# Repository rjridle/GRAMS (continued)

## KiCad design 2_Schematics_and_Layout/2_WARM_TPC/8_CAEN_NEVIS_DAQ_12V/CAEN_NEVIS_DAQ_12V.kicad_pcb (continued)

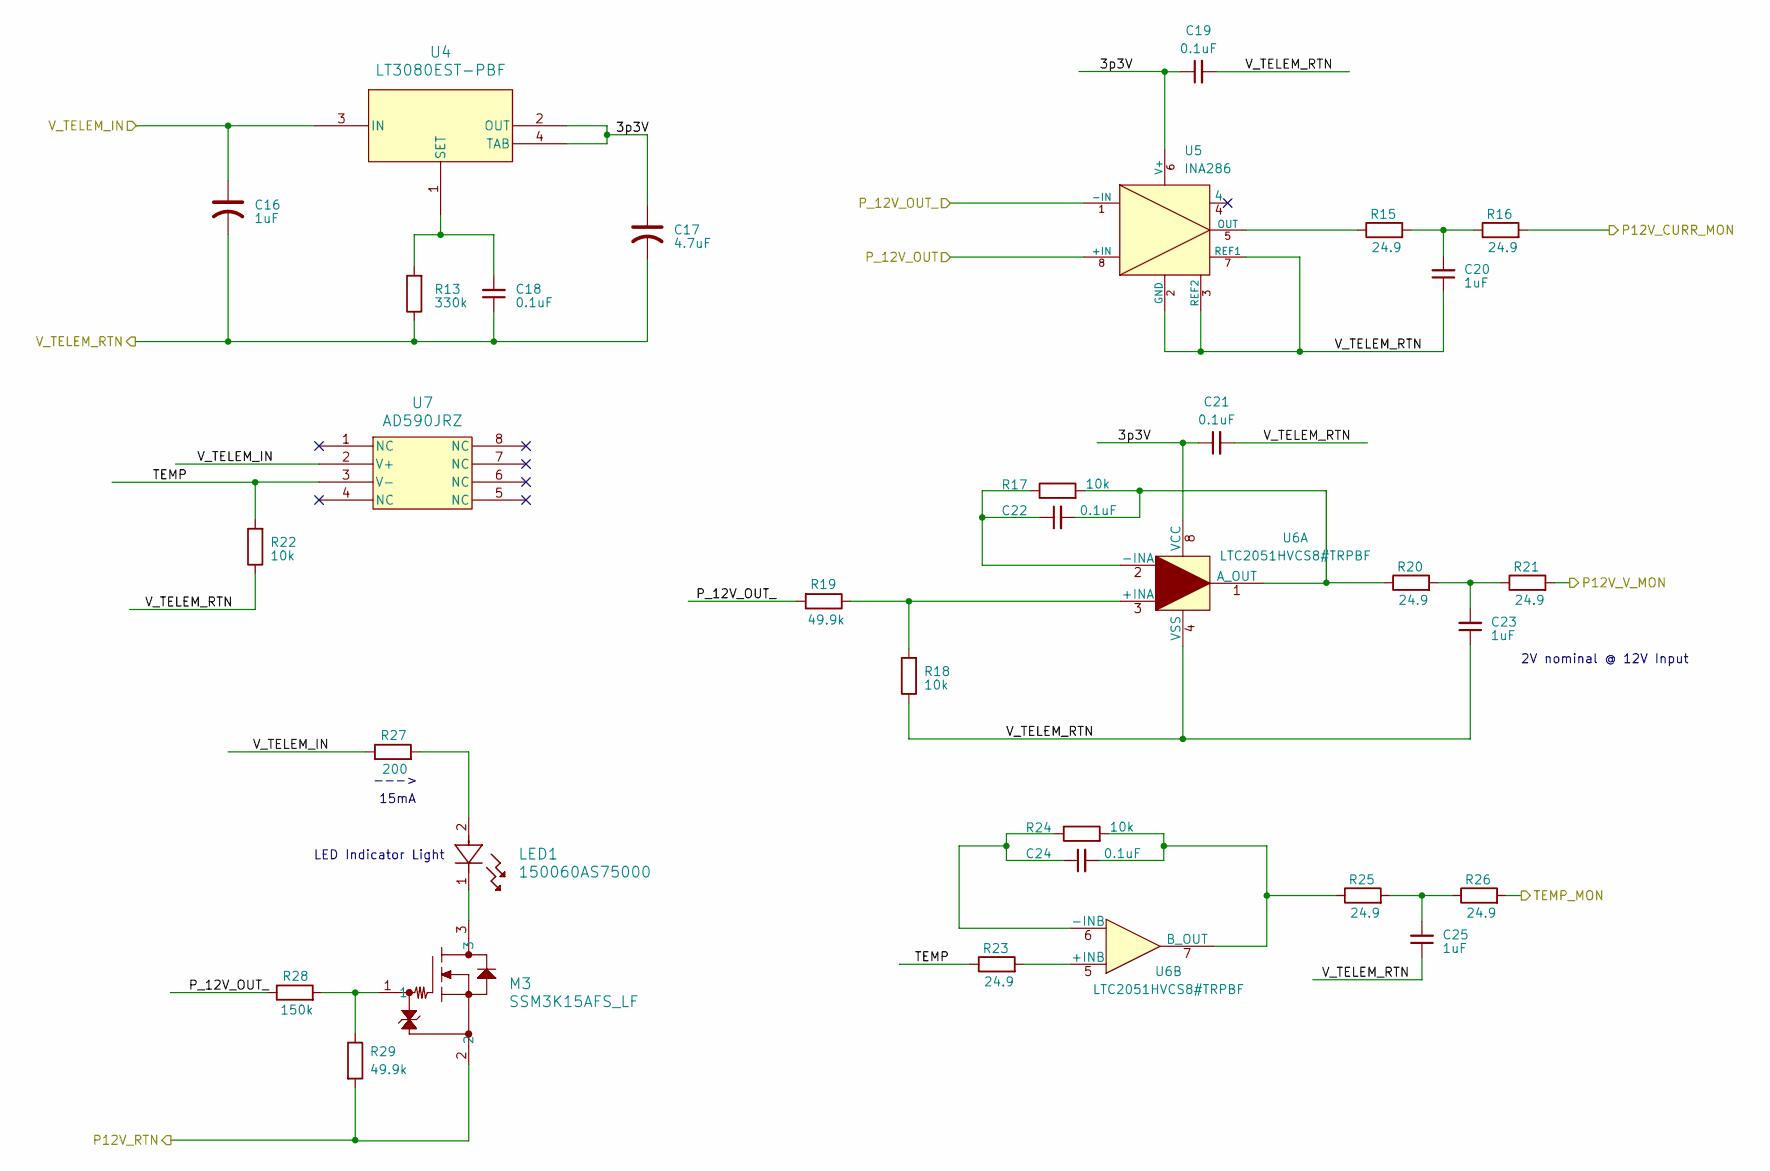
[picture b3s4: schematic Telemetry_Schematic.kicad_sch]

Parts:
C16: 1uF; CP_EIA-3216-10_Kemet-I; Man. Part Num TAJA105K016RNJ
C17: 4.7uF; CP_EIA-3216-10_Kemet-I; Man. Part Num TAJA475K016RNJ
C18: 0.1uF; C_0603_1608Metric; Man. Part Num CC0603KRX7R7BB104
C19, C21, C22, C24: 0.1uF; C_0402_1005Metric; Man. Part Num CL05B104KP5NNNC
C20, C23, C25: 1uF; C_0603_1608Metric; Man. Part Num CL10B105KO8NNNC
LED1: 150060AS75000; LED_0AS75000_WRE; Man. Part Num 150060AS75000
M3: SSM3K15AFS_LF; SSM_TOS; Man. Part Num SSM3K15AFS,LF
R13: 330k; R_0603_1608Metric; Man. Part Num ERA-3AEB334V
R15, R16, R20, R21, R23, R25, R26: 24.9; R_0603_1608Metric; Man. Part Num RNCF0603TKY24R9
R17, R24: 10k; R_0402_1005Metric; Man. Part Num RNCF0402BTE10K0
R18, R22: 10k; R_0603_1608Metric; Man. Part Num ERA-3AEB103V
R19: 49.9k; R_0603_1608Metric; Man. Part Num ERA-3AED4992V
R27: 200; R_0603_1608Metric; Man. Part Num RC0603JR-07200RL
R28: 150k; R_0603_1608Metric; Man. Part Num RK73B1JTTD154J
R29: 49.9k; R_0603_1608Metric; Man. Part Num RN73H1JTTD4992B10
U4: LT3080EST-PBF; SOT-3_ST_LIT; Man. Part Num LT3080EST#PBF
U5: INA286; INA28x_8SOIC; Man. Part Num INA286AIDR
U6: LTC2051HVCS8#TRPBF; R_8_ADI; Man. Part Num LTC2051HVCS8#TRPBF
U7: AD590JRZ; R_8_ADI; Man. Part Num AD590JRZ

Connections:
/P12V_I_MON: R16.2; also elsewhere on the board
/P12V_OUT: U5.8 (+IN); also elsewhere on the board
/P12V_OUT_: R19.2, R28.1, U5.1 (-IN); also elsewhere on the board
/P12V_V_MON: R21.2; also elsewhere on the board
/TEMP_MON: R26.2; also elsewhere on the board
/Telemetry_Schematic/3p3V: C17.1, C19.1, C21.1, U4.2 (OUT), U4.4 (TAB), U5.6 (V+), U6.8 (VCC)
/Telemetry_Schematic/TEMP: R22.2, R23.1, U7.3 (V-)
/V_SEC_RTN: M3.2, R29.2; also elsewhere on the board
/V_TELEM_IN: C16.1, R27.1, U4.3 (IN), U7.2 (V+); also elsewhere on the board
/V_TELEM_RTN: C16.2, C17.2, C18.1, C19.2, C20.1, C21.2, C23.1, C25.1, R13.1, R18.1, R22.1, U5.2 (GND), U5.3 (REF2), U5.7 (REF1), U6.4 (VSS); also elsewhere on the board
unnamed: C20.2, R15.2, R16.1
unnamed: C23.2, R20.2, R21.1
unnamed: C25.2, R25.2, R26.1
unnamed: LED1.1, M3.3
unnamed: LED1.2, R27.2
unnamed: M3.1, R28.2, R29.1
unnamed: C18.2, R13.2, U4.1 (SET)
unnamed: R15.1, U5.5 (OUT)
unnamed: R18.2, R19.1, U6.3 (+INA)
unnamed: C22.1, R17.1, U6.2 (-INA)
unnamed: C22.2, R17.2, R20.1, U6.1 (A_OUT)
unnamed: R23.2, U6.5 (+INB)
unnamed: C24.1, R24.1, U6.6 (-INB)
unnamed: C24.2, R24.2, R25.1, U6.7 (B_OUT)

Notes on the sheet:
--->
15mA
LED Indicator Light
2V nominal @ 12V Input

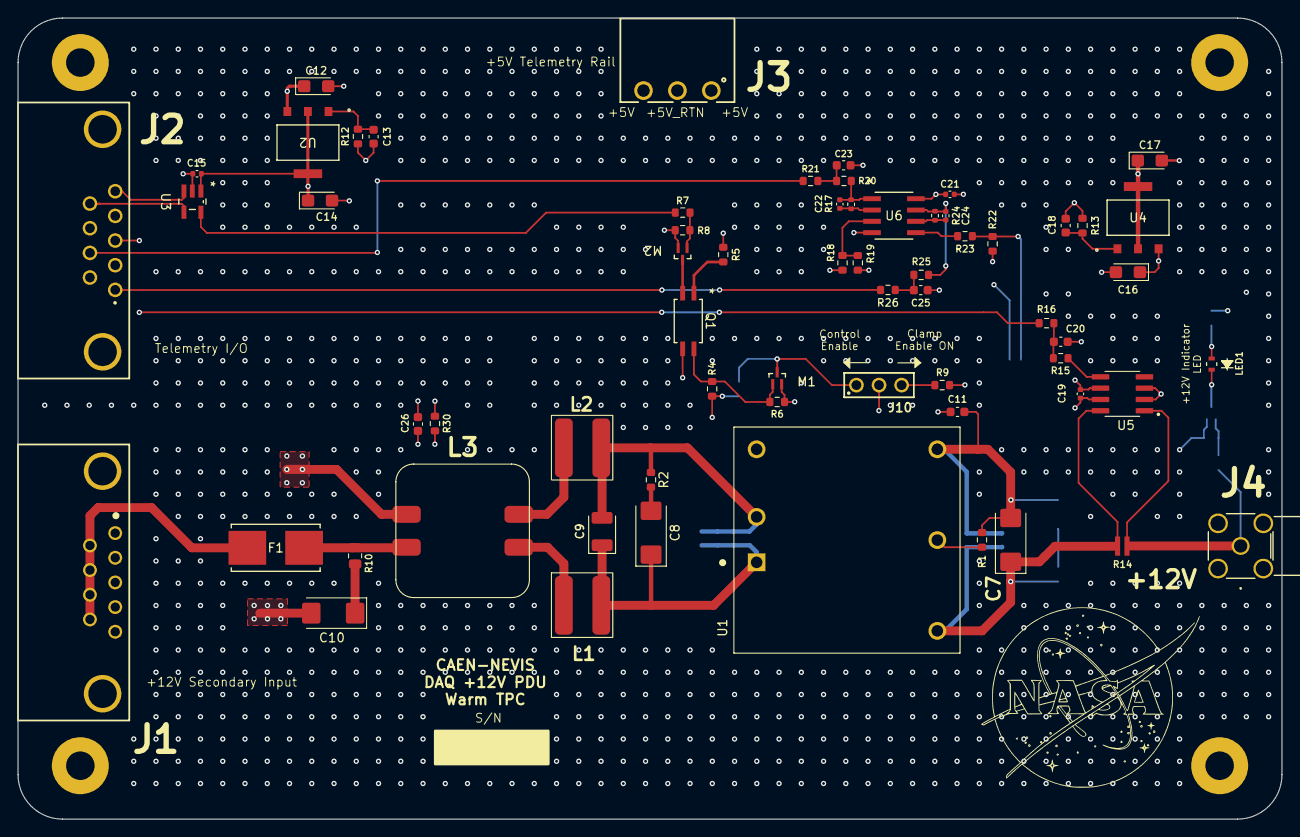
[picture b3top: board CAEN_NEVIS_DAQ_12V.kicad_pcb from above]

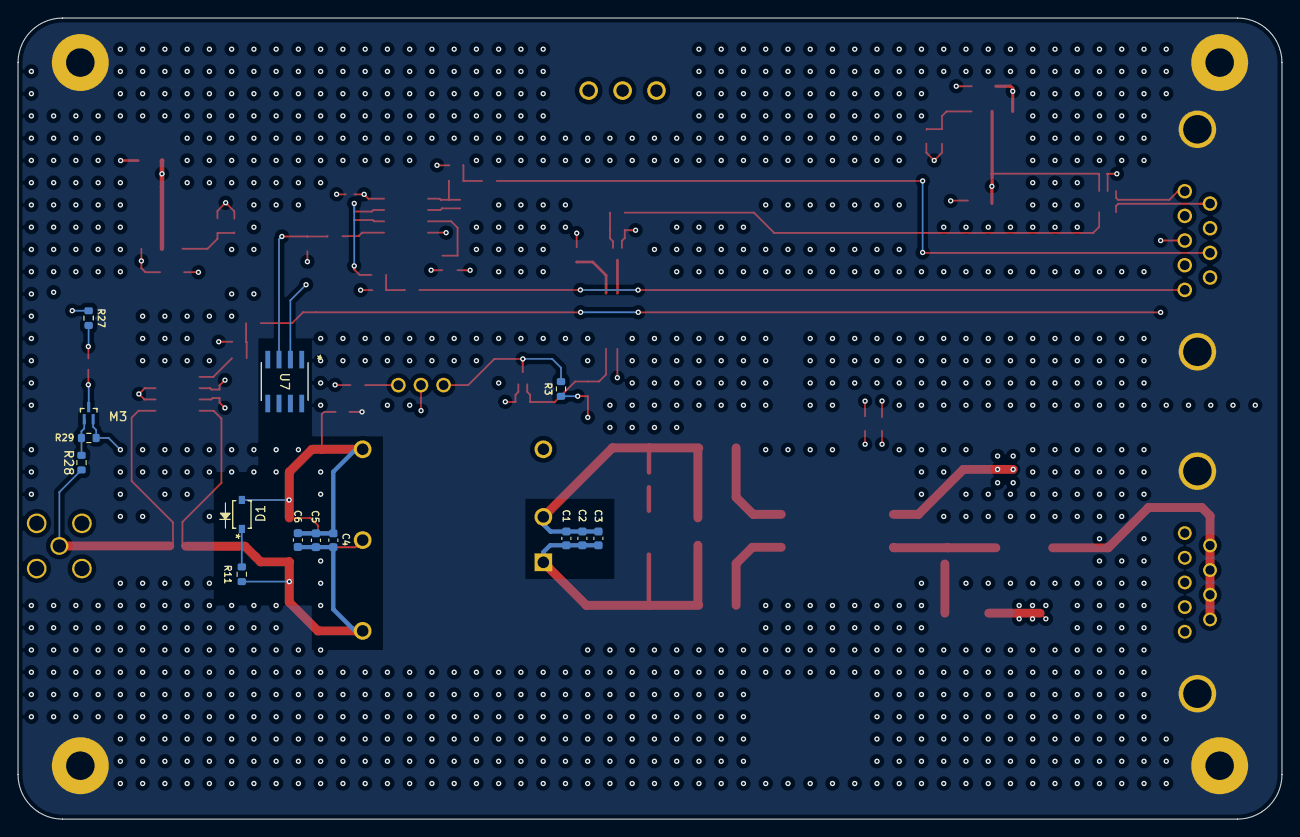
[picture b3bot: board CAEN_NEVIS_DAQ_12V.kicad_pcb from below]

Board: 6 copper layers, 142.0 x 90.0 mm, 82 parts (14 on the bottom side), 48 nets.

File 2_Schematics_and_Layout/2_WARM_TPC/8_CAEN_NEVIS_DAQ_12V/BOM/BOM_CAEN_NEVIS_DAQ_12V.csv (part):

"Reference","Qty","Manufacturer","Man. Part Num","Value","Distributor","Dist. Part Num","Footprint","DNP","Package","Part Type","Description"
"C1,C4","2","KEMET","C0603C103K5RACTU","0.01uF","Digi-Key","399-C0603C103K5RACTUCT-ND","Capacitor_SMD:C_0603_1608Metric","","0603 (1608 Metric)","SMD","10000 pF ±10% 50V Ceramic Capacitor X7R 0603 (1608 Metric)"
"C2,C5,C11,C26","4","YAGEO","CC0603KRX7R8BB104","0.1uF","Digi-Key","311-1341-1-ND","Capacitor_SMD:C_0603_1608Metric","","0603 (1608 Metric)","SMD","0.1 µF ±10% 25V Ceramic Capacitor X7R 0603 (1608 Metric)"
"C3,C6,C20,C23,C25","5","Samsung Electro-Mechanics","CL10B105KO8NNNC","1uF","Digi-Key","1276-1019-1-ND","Capacitor_SMD:C_0603_1608Metric","","0603 (1608 Metric)","SMD","0.1 µF ±10% 25V Ceramic Capacitor X7R 0603 (1608 Metric)"
"C7","1","KYOCERA AVX","TAJC106K025RNJ","10uF","Digi-Key","478-1700-1-ND","Capacitor_Tantalum_SMD:CP_EIA-6032-20_AVX-F","","2312 (6032 Metric)","SMD","10 µF Molded Tantalum Capacitors 25 V 2312 (6032 Metric) 1.8Ohm"
"C8,C10","2","KYOCERA AVX","TAJC107K016RNJ","100uF","Digi-Key","478-5258-1-ND","Capacitor_Tantalum_SMD:CP_EIA-6032-20_AVX-F","","2312 (6032 Metric)","SMD","100 µF Molded Tantalum Capacitors 16 V 2312 (6032 Metric) 1Ohm"
"C9","1","KEMET","T491B226K020AT","22uF","Digi-Key","399-5296-1-ND","Capacitor_Tantalum_SMD:CP_EIA-3528-12_Kemet-T","","1411 (3528 Metric)","SMD","22 µF Molded Tantalum Capacitors 20 V 1411 (3528 Metric) 4Ohm"
"C12,C16","2","KYOCERA AVX","TAJA105K016RNJ","1uF","Digi-Key","478-1649-1-ND","Capacitor_Tantalum_SMD:CP_EIA-3216-10_Kemet-I","","1206 (3216 Metric)","SMD","1 µF Molded Tantalum Capacitors 16 V 1206 (3216 Metric) 11Ohm"
"C13,C18","2","YAGEO","CC0603KRX7R7BB104","0.1uF","Digi-Key","311-1088-1-ND","Capacitor_SMD:C_0603_1608Metric","","0603 (1608 Metric)","SMD","0.1 µF ±10% 16V Ceramic Capacitor X7R 0603 (1608 Metric)"
"C14,C17","2","KYOCERA AVX","TAJA475K016RNJ","4.7uF","Digi-Key","478-3868-1-ND","Capacitor_Tantalum_SMD:CP_EIA-3216-10_Kemet-I","","1206 (3216 Metric)","SMD","4.7 µF Molded Tantalum Capacitors 16 V 1206 (3216 Metric) 4Ohm"
"C15,C19,C21,C22,C24","5","Samsung Electro-Mechanics","CL05B104KP5NNNC","0.1uF","Digi-Key","1276-1002-1-ND","Capacitor_SMD:C_0402_1005Metric","","0402 (1005 Metric)","SMD","0.1 µF ±10% 10V Ceramic Capacitor X7R 0402 (1005 Metric)"
"D1","1","onsemi","MMSZ13T1G","MMSZ13T1G (13V Zener)","Digi-Key","MMSZ13T1GOSCT-ND","ONSEMI:SOD-123_ONS-L","","SOD-123","SMD","Zener Diode 13 V 500 mW ±5% Surface Mount SOD-123"
"F1","1","Little Fuse","0154002.DR","0154002.DR","Digi-Key","F1224CT-ND","Little_Fuse:0154Series_LTF","","Surface Mount 2-SMD, Square End Block with Holder","SMD","2 A 125 V AC 125 V DC Fuse Board Mount (Cartridge Style Excluded) Requires Holder, Surface Mount 2-SMD, Square End Block with Holder"
"J1","1","Wurth Electronics","618009231221","618009231221","Digi-Key","732-618009231221-ND","Wurth_Elektronik:618009231221","","None","Through Hole","CONN D-SUB PLUG 9POS R/A SOLDER"
"J2","1","Würth Elektronik","618009231121","618009231121","Digi-Key","732-618009231121-ND","Wurth_Elektronik:618009231121","","-","Through Hole","CONN D-SUB RCPT 9POS R/A SOLDER"
"J3","1","Wurth Elektronik","691322310003","691322310003","Digi-Key","732-2089-ND","Wurth_Elektronik:691322310003","","-","Through Hole","3 Position Terminal Block Header, Male Pins, Shrouded (4 Side) 0.150"" (3.81mm) 90°, Right Angle Through Hole"
"J4","1","Adam Tech","RF2-49B-T-00-50-G-HDW","RF2-49B-T-00-50-G-HDW","Mouser","737-RF249BT0050GHDW","Adam_Tech:CONN_RF2-49B-T-00-50-G-HDW_ADM","","SMA","Through Hole","SMA Connector Jack, Female Socket 50 Ohms Through Hole, Right Angle Solder (Voltage Rating = 335V)"
"J10","1","Würth Elektronik","61300311121","61300311121","Digi-Key","732-5316-ND","Wurth_Elektronik:61300311121","","","Through Hole","Connector Header Through Hole 3 position 0.100"" (2.54mm)"
"L1,L2","2","Coil Craft","LPS6235-822MR","8.2uH (+/- 20%)","Coil Craft","LPS6235-822MR","CoilCraft:LPS6235-822MR","","-","SMD","Shielded Power Inductors – LPS6235"
"L3","1","Coil Craft","MSD1583-105KE_","900uH to 1mH (CM) 2uH Leakage","Coil Craft","MSD1583-105KE_","CoilCraft:MSD1583-105","","","SMD","Common Mode Chokes – MSD1583"
"LED1","1","Würth Elektronik","150060AS75000","150060AS75000","Digi-Key","732-150060AS75000CT-ND","Wurth_Elektronik:LED_0AS75000_WRE","","0603","SMD","LED AMBER CLEAR 0603 SMD"
"M1,M2,M3","3","Toshiba Semiconductor and Storage","SSM3K15AFS,LF","SSM3K15AFS_LF","Digi-Key","SSM3K15AFSLFCT-ND","Toshiba_Semi:SSM_TOS","","SSM_TOS","SMD","MOSFET N-CH 30V 100MA SSM"
"Q1","1","Isocom Components 2004 LTD","ISP281D","ISP281D","Digi-Key","58-ISP281DCT-ND","ISOCOM:ISP281D_ISO","","4-SOP","SMD","Optoisolator Transistor Output 3750Vrms 1 Channel 4-SOP"
"R1","1","","","(DNP)","Digi-Key","","Resistor_SMD:R_0603_1608Metric","DNP","","SMD",""
"R2","1","YAGEO","RL0805FR-070R1L","0.1","Digi-Key","311-.10SCT-ND","Resistor_SMD:R_0603_1608Metric","","0805 (2012 Metric)","SMD","100 mOhms ±1% 0.125W, 1/8W Chip Resistor 0805 (2012 Metric) Current Sense Thick Film"
"R3","1","Panasonic Electronic Components","ERA-3AEB203V","20k","Digi-Key","P20KDBCT-ND","Resistor_SMD:R_0603_1608Metric","","0603 (1608 Metric)","SMD","20 kOhms ±0.1% 0.1W, 1/10W Chip Resistor 0603 (1608 Metric) Automotive AEC-Q200 Thin Film"
"R4","1","Panasonic Electronic Components","ERA-3AEB153V","15k","Digi-Key","P15KDBCT-ND","Resistor_SMD:R_0603_1608Metric","","0603 (1608 Metric)","SMD","15 kOhms ±0.1% 0.1W, 1/10W Chip Resistor 0603 (1608 Metric) Automotive AEC-Q200 Thin Film"
"R5","1","Vishay Dale","TNPW0603180RBEEA","180","Digi-Key","541-4531-1-ND","Resistor_SMD:R_0603_1608Metric","","0603 (1608 Metric)","SMD","180 Ohms ±0.1% 0.21W Chip Resistor 0603 (1608 Metric) Anti-Sulfur, Automotive AEC-Q200, Moisture Resistant Thin Film"
"R6","1","YAGEO","RT0603BRE075KL","5k","Digi-Key","13-RT0603BRE075KLCT-ND","Resistor_SMD:R_0603_1608Metric","","0603 (1608 Metric)","SMD","5 kOhms ±0.1% 0.1W, 1/10W Chip Resistor 0603 (1608 Metric) Thin Film"
"R7","1","KOA Speer Electronics, Inc.","RN73H1JTTD8350A05","835","Digi-Key","2019-RN73H1JTTD8350A05CT-ND","Resistor_SMD:R_0603_1608Metric","","0603 (1608 Metric)","SMD","835 Ohms ±0.05% 0.1W, 1/10W Chip Resistor 0603 (1608 Metric) Automotive AEC-Q200, Moisture Resistant Metal Film"
"R8,R30","2","Stackpole Electronics Inc","RMCF0603FT1K00","1k","Digi-Key","RMCF0603FT1K00CT-ND","Resistor_SMD:R_0603_1608Metric","","0603 (1608 Metric)","SMD","1 kOhms ±1% 0.1W, 1/10W Chip Resistor 0603 (1608 Metric) Automotive AEC-Q200 Thick Film"
"R9,R11","2","Vishay Dale","TNPW060349R9BEEA","49.9","Digi-Key","541-2031-1-ND","Resistor_SMD:R_0603_1608Metric","","0603 (1608 Metric)","SMD","49.9 Ohms ±0.1% 0.21W Chip Resistor 0603 (1608 Metric) Anti-Sulfur, Automotive AEC-Q200, Moisture Resistant Thin Film"
"R10","1","TE Connectivity Passive Product","CRGH0805F10R","10","Digi-Key","A126420CT-ND","Resistor_SMD:R_0805_2012Metric","","0805 (2012 Metric)","SMD","10 Ohms ±1% 0.333W, 1/3W Chip Resistor 0805 (2012 Metric) Automotive AEC-Q200 Thick Film"
"R12,R13","2","Panasonic Electronic Components","ERA-3AEB334V","330k","Digi-Key","P330KDBCT-ND","Resistor_SMD:R_0603_1608Metric","","0603 (1608 Metric)","SMD","330 kOhms ±0.1% 0.1W, 1/10W Chip Resistor 0603 (1608 Metric) Automotive AEC-Q200 Thin Film"
"R14","1","Ohmite","FCSL20R010FER","FCSL20R010FER","Digi-Key","FCSL20R010FERCT-ND","Foil_Resistors:RES_FCSL20_OHM-L","","0805 (2012 Metric)","SMD","10 mOhms ±1% 1W Chip Resistor Wide 0805 (2012 Metric), 0508 Current Sense, Moisture Resistant Metal Foil"
"R15,R16,R20,R21,R23,R25,R26","7","Stackpole Electronics Inc","RNCF0603TKY24R9","24.9","Digi-Key","RNCF0603TKY24R9CT-ND","Resistor_SMD:R_0603_1608Metric","","0603 (1608 Metric)","SMD","24.9 Ohms ±0.01% 0.1W, 1/10W Chip Resistor 0603 (1608 Metric) Automotive AEC-Q200 Thin Film"
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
